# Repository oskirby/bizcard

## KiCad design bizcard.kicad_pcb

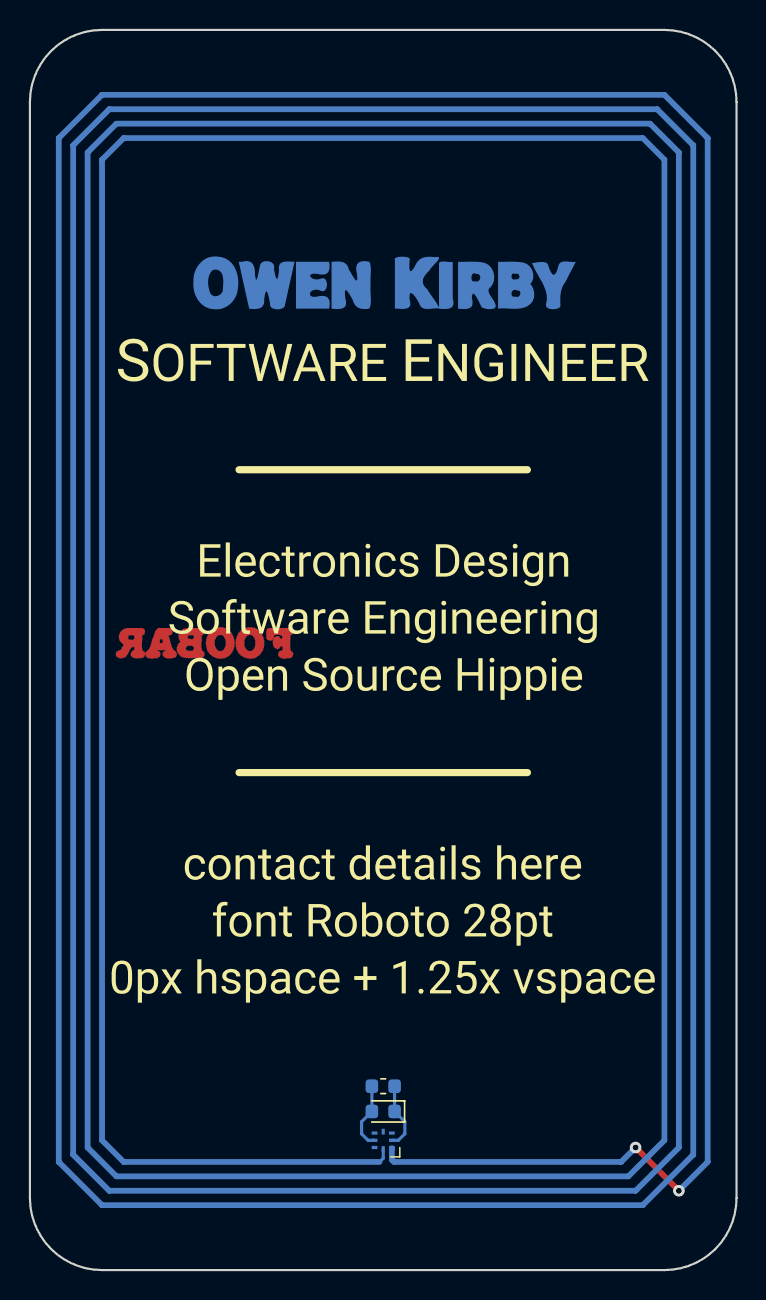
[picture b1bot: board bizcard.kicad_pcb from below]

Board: 2 copper layers, 49.0 x 86.0 mm, 7 parts (6 on the bottom side), 3 nets.

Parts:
C1: C; C_0603_1608Metric
D1: LED_ALT; LED_0603_1608Metric
IC1: NT3H2111; XQFN8
contact: contact
name-title: name-title
subtitle: subtitle
wordsearch: wordsearch

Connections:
/NFC_COIL: IC1.1, IC1.8
unnamed: C1.1, D1.2, IC1.6
unnamed: C1.2, D1.1, IC1.2

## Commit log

2020-02-18 Add KiCAD project for PCB business cards.
